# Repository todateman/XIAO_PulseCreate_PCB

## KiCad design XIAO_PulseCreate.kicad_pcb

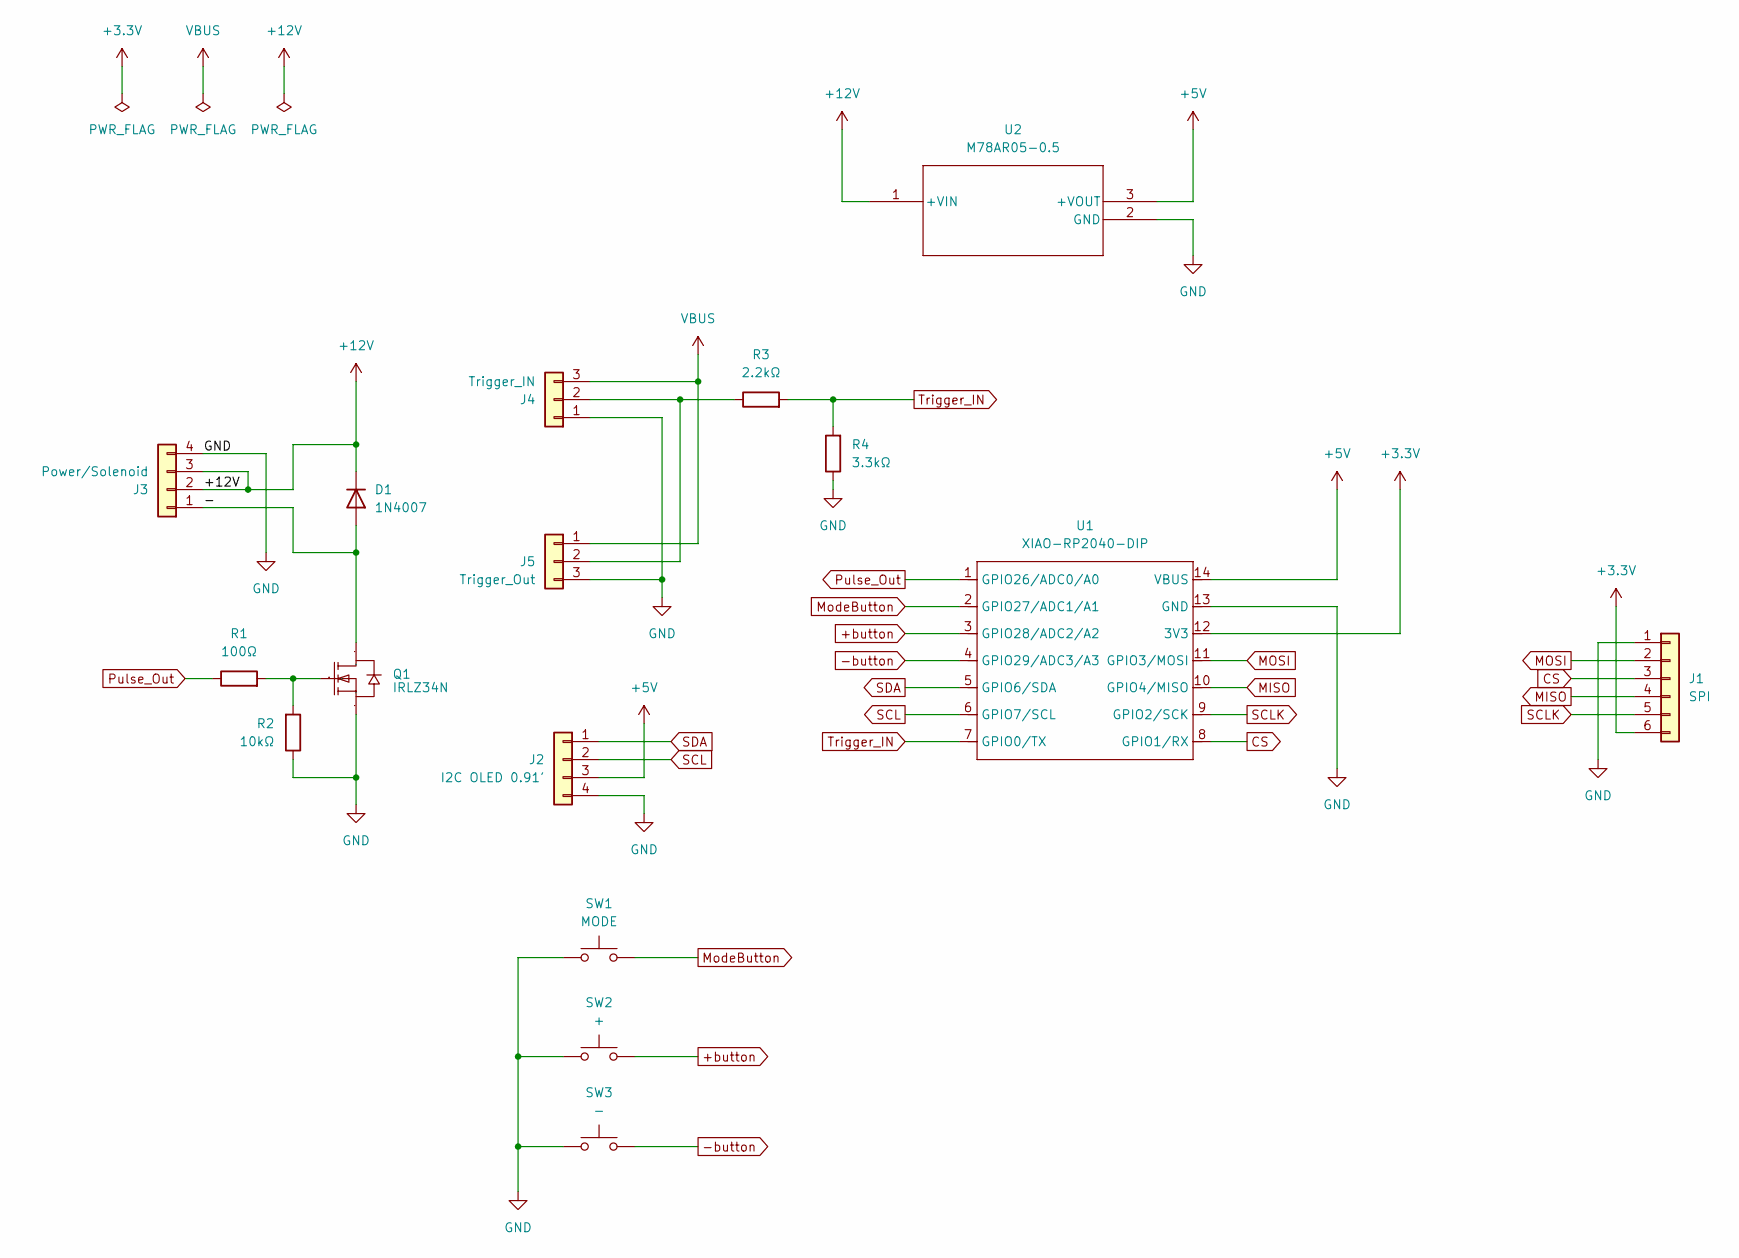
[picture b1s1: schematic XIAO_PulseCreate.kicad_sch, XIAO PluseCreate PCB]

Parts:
D1: 1N4007; D_DO-41_SOD81_P10.16mm_Horizontal
J1: SPI; PinSocket_1x06_P2.54mm_Vertical
J2: I2C OLED 0.91'; PinSocket_1x04_P2.54mm_Vertical
J3: Power/Solenoid; ML-950-4P
J4: Trigger_IN; JST_XH_B3B-XH-A_1x03_P2.50mm_Vertical
J5: Trigger_Out; JST_EH_B3B-EH-A_1x03_P2.50mm_Vertical
Q1: IRLZ34N; TO-220F-3_L10.2-W4.7-P2.54-L; Manufacturer Part 2SK2232-VB; LCSC Part Name 1个N沟道 耐压:60V 电流:45A
R1: 100Ω; R_Axial_DIN0207_L6.3mm_D2.5mm_P10.16mm_Horizontal
R2: 10kΩ; R_Axial_DIN0207_L6.3mm_D2.5mm_P10.16mm_Horizontal
R3: 2.2kΩ; R_Axial_DIN0207_L6.3mm_D2.5mm_P10.16mm_Horizontal
R4: 3.3kΩ; R_Axial_DIN0207_L6.3mm_D2.5mm_P10.16mm_Horizontal
SW1: MODE; SW_PUSH_1P1T_6x3.5mm_H4.3_APEM_MJTP1243
SW2: +; SW_PUSH_1P1T_6x3.5mm_H4.3_APEM_MJTP1243
SW3: -; SW_PUSH_1P1T_6x3.5mm_H4.3_APEM_MJTP1243
U1: XIAO-RP2040-DIP
U2: M78AR05-0.5; SIP3_M78AR-0.5_MIN

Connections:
+3.3V: J1.6, U1.12 (3V3)
+5V: J2.3, U1.14 (VBUS), U2.3 (+VOUT)
+12V: D1.1 (K), J3.2, J3.3, U2.1 (+VIN)
+button: SW2.1, U1.3 (GPIO28/ADC2/A2)
-button: SW3.1, U1.4 (GPIO29/ADC3/A3)
/-: D1.2 (A), J3.1, Q1.2 (D)
CS: J1.3, U1.8 (GPIO1/RX)
GND: J1.1, J2.4, J3.4, J4.1, J5.3, Q1.3 (S), R2.1, R4.1, SW1.2, SW2.2, SW3.2, U1.13 (GND), U2.2 (GND)
MISO: J1.4, U1.10 (GPIO4/MISO)
MOSI: J1.2, U1.11 (GPIO3/MOSI)
ModeButton: SW1.1, U1.2 (GPIO27/ADC1/A1)
unnamed: J4.2, J5.2, R3.1
unnamed: Q1.1 (G), R1.2, R2.2
Pulse_Out: R1.1, U1.1 (GPIO26/ADC0/A0)
SCL: J2.2, U1.6 (GPIO7/SCL)
SCLK: J1.5, U1.9 (GPIO2/SCK)
SDA: J2.1, U1.5 (GPIO6/SDA)
Trigger_IN: R3.2, R4.2, U1.7 (GPIO0/TX)
VBUS: J4.3, J5.1

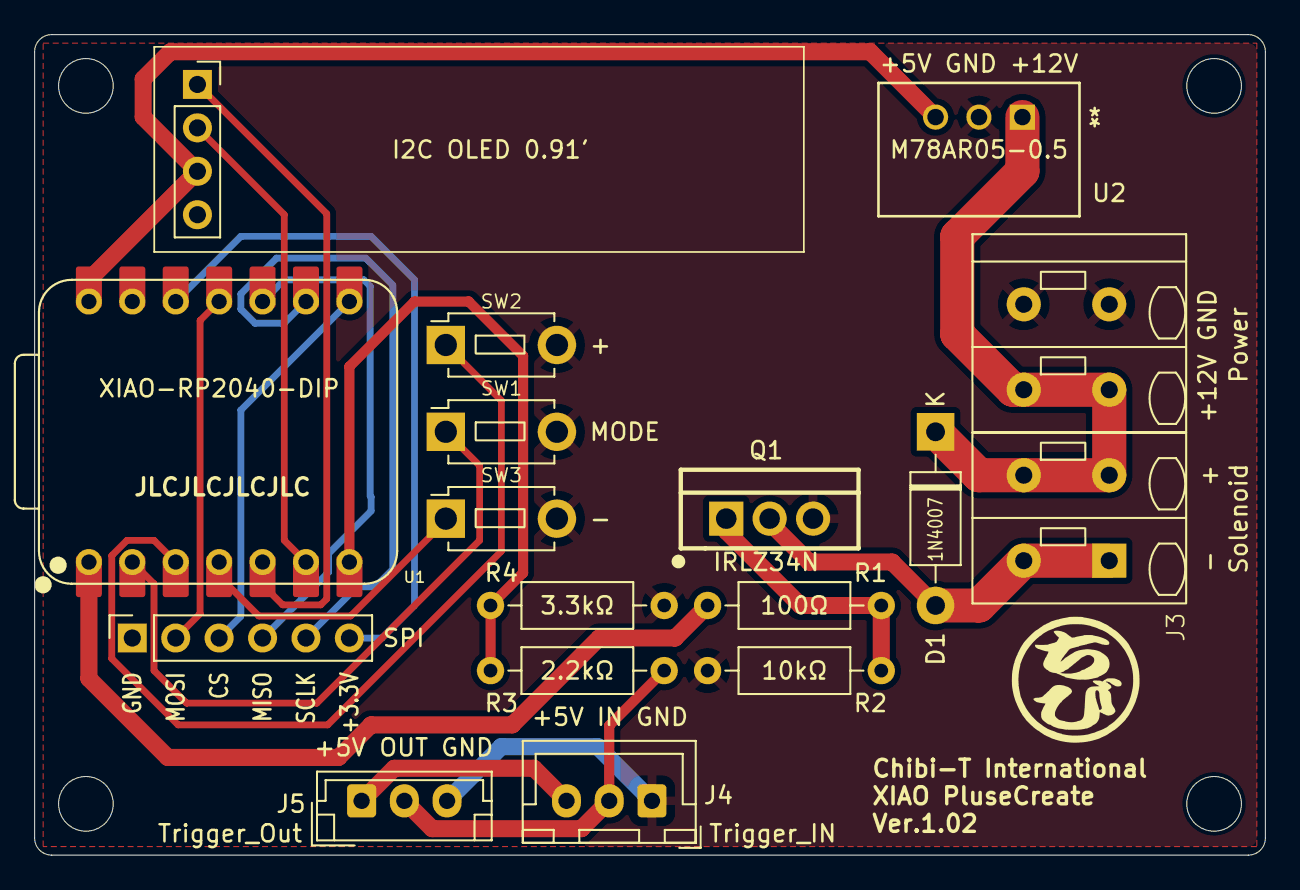
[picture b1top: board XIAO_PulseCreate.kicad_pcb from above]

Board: 2 copper layers, 72.0 x 48.0 mm, 20 parts (0 on the bottom side), 19 nets.

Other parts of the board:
MH1, MH1#2, MH1#3, MH1#4: MountingHole_3.2mm_M3

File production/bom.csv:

Designator,Footprint,Quantity,Value,LCSC Part #
D1,D_DO-41_SOD81_P10.16mm_Horizontal,1,1N4007,
J1,PinSocket_1x06_P2.54mm_Vertical,1,SPI,
J3,ML-950-4P,1,Power/Solenoid,
J4,JST_XH_B3B-XH-A_1x03_P2.50mm_Vertical,1,Trigger_IN,
J5,JST_EH_B3B-EH-A_1x03_P2.50mm_Vertical,1,Trigger_Out,
Q1,TO-220F-3_L10.2-W4.7-P2.54-L,1,IRLZ34N,
R1,R_Axial_DIN0207_L6.3mm_D2.5mm_P10.16mm_Horizontal,1,100Ω,
R2,R_Axial_DIN0207_L6.3mm_D2.5mm_P10.16mm_Horizontal,1,10kΩ,
R3,R_Axial_DIN0207_L6.3mm_D2.5mm_P10.16mm_Horizontal,1,2.2kΩ,
R4,R_Axial_DIN0207_L6.3mm_D2.5mm_P10.16mm_Horizontal,1,3.3kΩ,
SW1,SW_PUSH_1P1T_6x3.5mm_H4.3_APEM_MJTP1243,1,MODE,
SW2,SW_PUSH_1P1T_6x3.5mm_H4.3_APEM_MJTP1243,1,+,
SW3,SW_PUSH_1P1T_6x3.5mm_H4.3_APEM_MJTP1243,1,-,
U1,XIAO-RP2040-DIP,1,XIAO-RP2040-DIP,
U2,SIP3_M78AR-0.5_MIN,1,M78AR05-0.5,

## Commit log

2025-02-11 first
2025-02-11 Trigger_INの分圧抵抗を追加。 基板のソレノイドと電源の表記が逆だったので修正
2025-02-11 MOSFETのヒートシンク取付を想定しレイアウト変更
2025-02-19 MOSFETをIRLZ34Nに変更
2025-02-26 .kicad_sch-bakファイルを.gitignoreに追加
